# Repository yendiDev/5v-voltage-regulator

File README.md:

# 5V 1A Voltage Regulator with LM7805 IC

A custom voltage regulator that takes in a 12V 1A input and outputs 5V 1A, suitable for most electronic projects. It uses DC jack barrels as connectors, as can be seen in the 3D version of it below. 

Below are screenshots of the PCB:

### Schematics:

### PCB Layout:
First layer:

Bottom layer:

### 3D view of PCB:

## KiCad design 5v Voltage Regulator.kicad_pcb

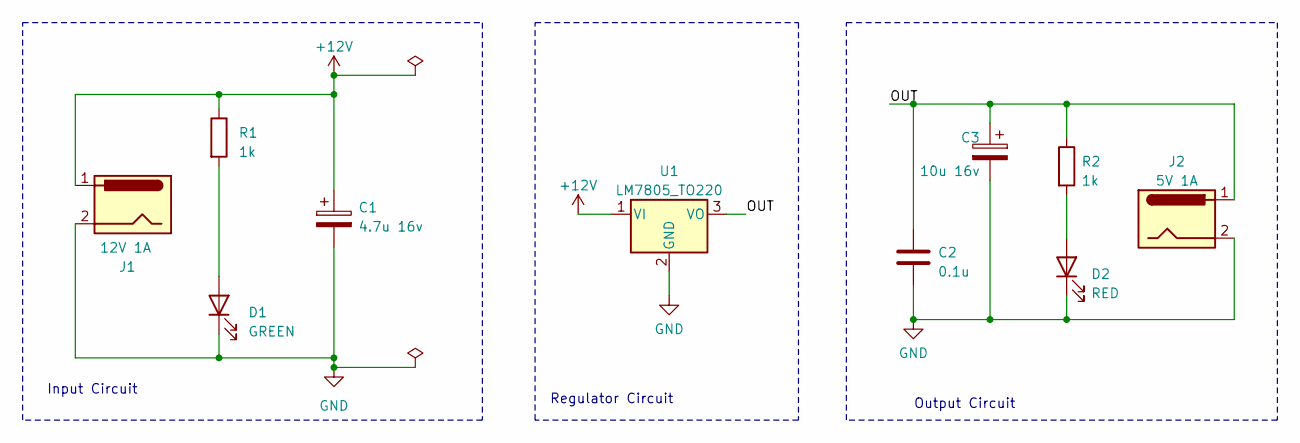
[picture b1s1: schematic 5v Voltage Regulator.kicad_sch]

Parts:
C1: 4.7u 16v; CP_Axial_L10.0mm_D4.5mm_P15.00mm_Horizontal
C2: 0.1u; CP_Axial_L10.0mm_D4.5mm_P15.00mm_Horizontal
C3: 10u 16v; CP_Axial_L10.0mm_D4.5mm_P15.00mm_Horizontal
D1: GREEN; LED_D3.0mm
D2: RED; LED_D3.0mm
J1: 12V 1A; BarrelJack_CUI_PJ-063AH_Horizontal
J2: 5V 1A; BarrelJack_CUI_PJ-063AH_Horizontal
R1, R2: 1k; R_Axial_DIN0204_L3.6mm_D1.6mm_P5.08mm_Horizontal
U1: LM7805_TO220; TO-220-3_Vertical

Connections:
+12V: C1.1, J1.1, R1.1, U1.1 (VI)
/OUT: C2.1, C3.1, J2.1, R2.1, U1.3 (VO)
GND: C1.2, C2.2, C3.2, D1.1 (K), D2.1 (K), J1.2, J2.2, U1.2 (GND)
unnamed: D1.2 (A), R1.2
unnamed: D2.2 (A), R2.2

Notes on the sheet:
Output Circuit
Regulator Circuit
Input Circuit

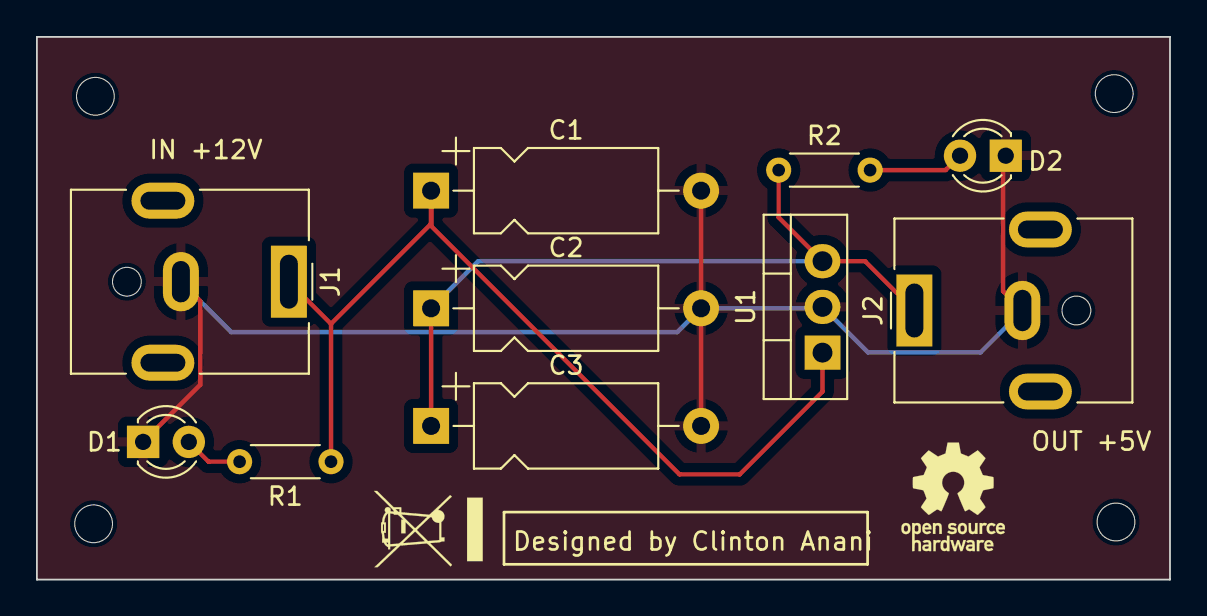
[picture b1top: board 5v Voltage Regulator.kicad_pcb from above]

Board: 2 copper layers, 62.9 x 30.2 mm, 10 parts (0 on the bottom side), 5 nets.
